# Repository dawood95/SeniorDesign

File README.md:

# SeniorDesign
Senior Design Repo

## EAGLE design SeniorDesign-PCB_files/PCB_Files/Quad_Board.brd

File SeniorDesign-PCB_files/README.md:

# Senior Design
Team 9's (Spring 2015) senior design repository.

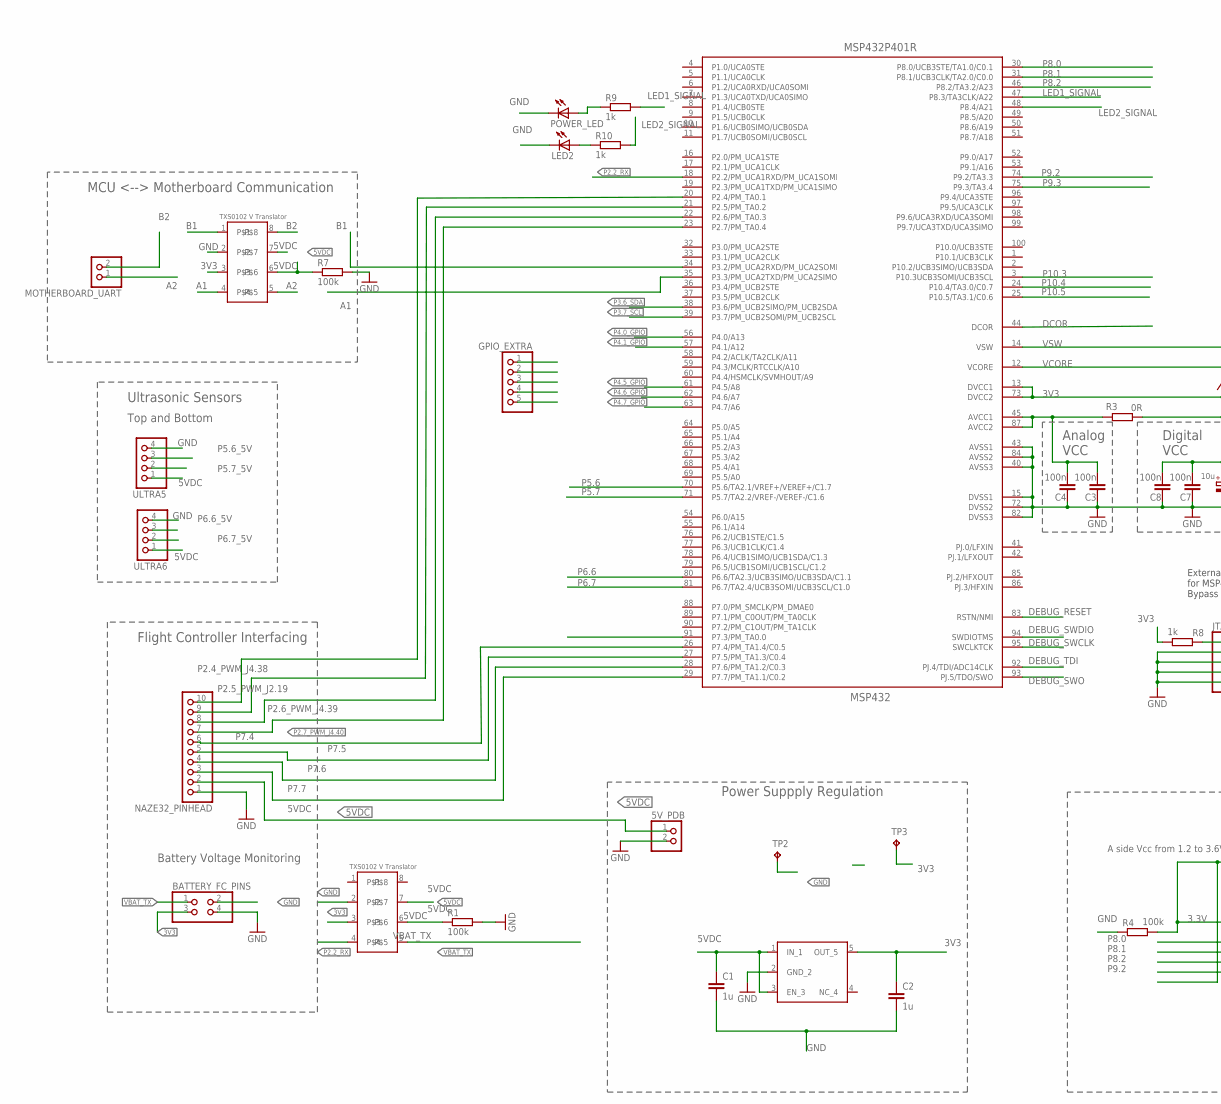
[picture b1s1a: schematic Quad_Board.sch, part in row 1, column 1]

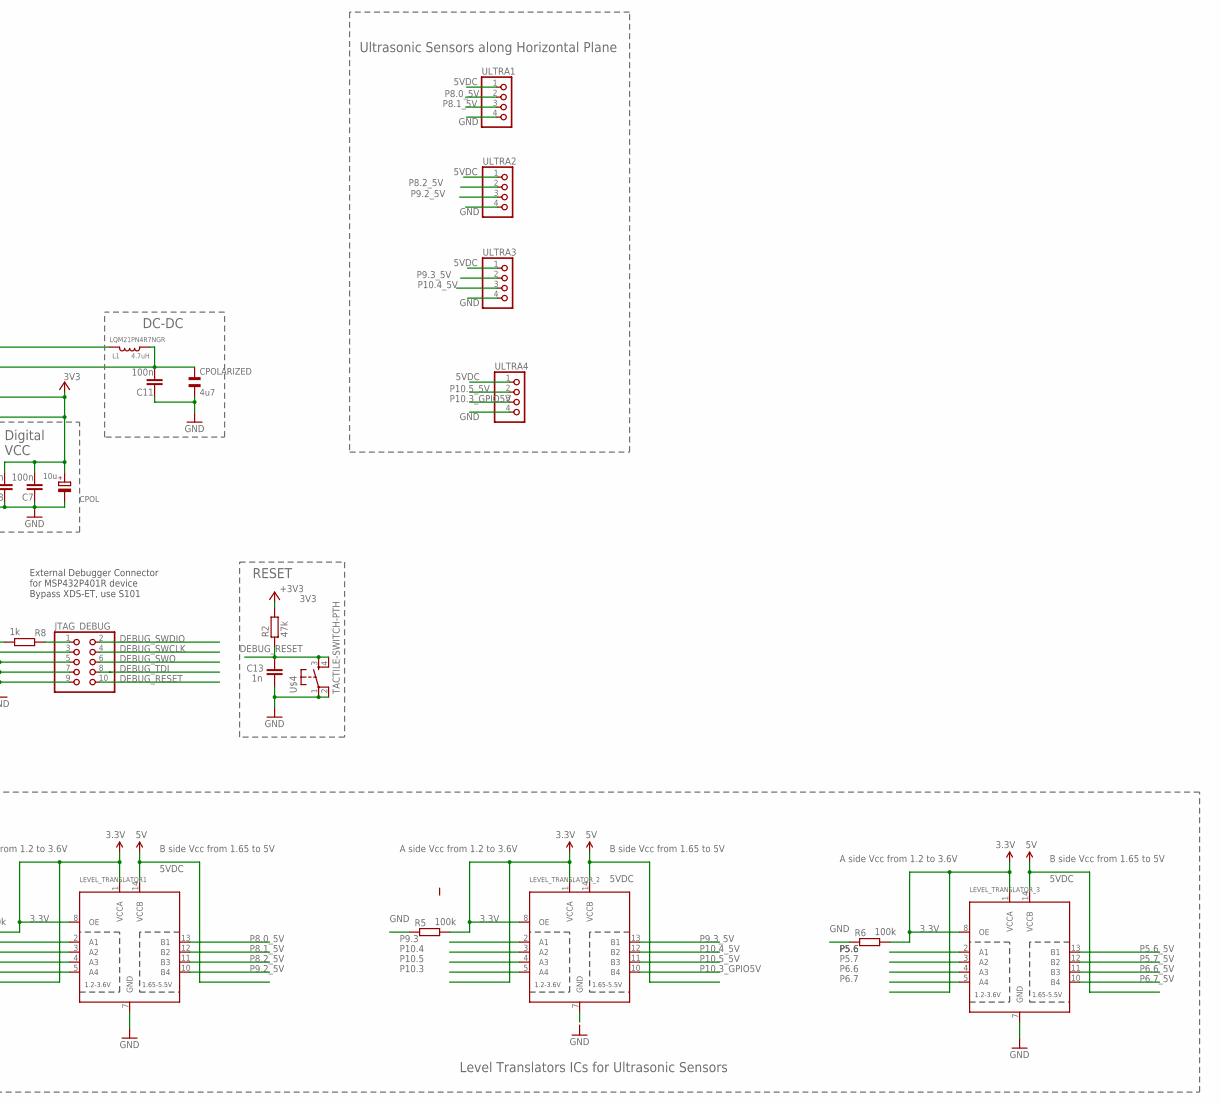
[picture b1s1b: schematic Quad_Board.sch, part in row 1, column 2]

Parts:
5V_PDB: PINHD-1X2; 1X02
BATTERY_FC_PINS: PINHD-2X2; 2X02
C1, C2: 1u; C0805
C3, C4, C7, C8, C11: 100n; C0805
C13: 1n; C0805
CPOL: 10u; A/3216-18R
CPOLARIZED: 4u7; CSMD0805
GPIO_EXTRA: PINHD-1X5; 1X05
JTAG_DEBUG: PINHD-2X5; 2X05
L1: 4.7uH; 0806
LED2: LED_E; LED_1206
LEVEL_TRANSLATOR1: TXB0104PWRSOIC14; SO14
LEVEL_TRANSLATOR_2, LEVEL_TRANSLATOR_3: TXB0104PWRSOIC14; SO14
MOTHERBOARD_UART: PINHD-1X2; 1X02
MSP432P401R: MSP432; PZ100
NAZE32_PINHEAD: PINHD-1X10; 1X10
POWER_LED: LED_E; LED_1206
R1, R4, R5, R6, R7: 100k; M1206
R2: 47k; R1206
R3: 0R; 0402
R8: 1k; R1206
R9, R10: 1k; M0805
TP2, TP3: TPB2,54; B2,54
U$1, U$3: TXS0102; DCT_R-PDSO-G8
U$2: TLV733P; SOT23-5
U$4: TACTILE-SWITCH-PTH; TAC-SWITCH-PTH
ULTRA1, ULTRA2, ULTRA3, ULTRA4, ULTRA5, ULTRA6: PINHD-1X4; 1X04

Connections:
3.3V: LEVEL_TRANSLATOR1.1 (VCCA), LEVEL_TRANSLATOR1.8 (OE), LEVEL_TRANSLATOR_2.1 (VCCA), LEVEL_TRANSLATOR_2.8 (OE), LEVEL_TRANSLATOR_3.1 (VCCA), LEVEL_TRANSLATOR_3.8 (OE), R4.2, R5.2, R6.2
3V3: BATTERY_FC_PINS.3, C2.1, C7.1, C8.1, CPOL.+, MSP432P401R.13 (DVCC1), MSP432P401R.73 (DVCC2), R2.2, R3.1, R8.1, TP3.TP, U$1.3, U$2.5 (OUT_5), U$3.3
5VDC: 5V_PDB.1, C1.1, LEVEL_TRANSLATOR1.14 (VCCB), LEVEL_TRANSLATOR_2.14 (VCCB), LEVEL_TRANSLATOR_3.14 (VCCB), NAZE32_PINHEAD.2, R1.1, R7.1, U$1.6, U$1.7, U$2.1 (IN_1), U$2.3 (EN_3), U$3.6, U$3.7, ULTRA1.1, ULTRA2.1, ULTRA3.1, ULTRA4.1, ULTRA5.1, ULTRA6.1
A1: MSP432P401R.35 (P3.3/PM_UCA2TXD/PM_UCA2SIMO), U$1.4
A2: MOTHERBOARD_UART.1, U$1.5
B1: MSP432P401R.34 (P3.2/PM_UCA2RXD/PM_UCA2SOMI), U$1.1
B2: MOTHERBOARD_UART.2, U$1.8
DCOR: MSP432P401R.44 (DCOR)
DEBUG_RESET: C13.1, JTAG_DEBUG.10, MSP432P401R.83 (RSTN/NMI), R2.1, U$4.3, U$4.4
DEBUG_SWCLK: JTAG_DEBUG.4, MSP432P401R.95 (SWCLKTCK)
DEBUG_SWDIO: JTAG_DEBUG.2, MSP432P401R.94 (SWDIOTMS)
DEBUG_SWO: JTAG_DEBUG.6, MSP432P401R.93 (PJ.5/TDO/SWO)
DEBUG_TDI: JTAG_DEBUG.8, MSP432P401R.92 (PJ.4/TDI/ADC14CLK)
GND: 5V_PDB.2, BATTERY_FC_PINS.2, BATTERY_FC_PINS.4, C1.2, C2.2, C3.2, C4.2, C7.2, C8.2, C11.2, C13.2, CPOL.-, CPOLARIZED.2, JTAG_DEBUG.3, JTAG_DEBUG.5, JTAG_DEBUG.7, JTAG_DEBUG.9, LED2.C, LEVEL_TRANSLATOR1.7 (GND), LEVEL_TRANSLATOR_2.7 (GND), LEVEL_TRANSLATOR_3.7 (GND), MSP432P401R.15 (DVSS1), MSP432P401R.40 (AVSS3), MSP432P401R.43 (AVSS1), MSP432P401R.72 (DVSS2), MSP432P401R.82 (DVSS3), MSP432P401R.84 (AVSS2), NAZE32_PINHEAD.1, POWER_LED.C, R1.2, R4.1, R5.1, R6.1, R7.2, TP2.TP, U$1.2, U$2.2 (GND_2), U$3.2, U$4.1, U$4.2, ULTRA1.4, ULTRA2.4, ULTRA3.4, ULTRA4.4, ULTRA5.4, ULTRA6.4
LED1_SIGNAL: MSP432P401R.47 (P8.3/TA3CLK/A22), R9.2
LED2_SIGNAL: MSP432P401R.48 (P8.4/A21), R10.2
unnamed: C3.1, C4.1, MSP432P401R.45 (AVCC1), MSP432P401R.87 (AVCC2), R3.2
unnamed: POWER_LED.A, R9.1
unnamed: LED2.A, R10.1
unnamed: JTAG_DEBUG.1, R8.2
P1.0/UCA0STE: MSP432P401R.4 (P1.0/UCA0STE)
P1.1/UCA0CLK: MSP432P401R.5 (P1.1/UCA0CLK)
P1.2/UCA0RXD/UCA0SOMI: MSP432P401R.6 (P1.2/UCA0RXD/UCA0SOMI)
P1.3/UCA0TXD/UCA0SIMO: MSP432P401R.7 (P1.3/UCA0TXD/UCA0SIMO)
P1.4/UCB0STE: MSP432P401R.8 (P1.4/UCB0STE)
P1.5/UCB0CLK: MSP432P401R.9 (P1.5/UCB0CLK)
P1.6/UCB0SIMO/UCB0SDA: MSP432P401R.10 (P1.6/UCB0SIMO/UCB0SDA)
P1.7/UCB0SOMI/UCB0SCL: MSP432P401R.11 (P1.7/UCB0SOMI/UCB0SCL)
P2.0/PM_UCA1STE: MSP432P401R.16 (P2.0/PM_UCA1STE)
P2.1/PM_UCA1CLK: MSP432P401R.17 (P2.1/PM_UCA1CLK)
P2.2_RX: MSP432P401R.18 (P2.2/PM_UCA1RXD/PM_UCA1SOMI), U$3.4
P2.3/PM_UCA1TXD/PM_UCA1SIMO: MSP432P401R.19 (P2.3/PM_UCA1TXD/PM_UCA1SIMO)
P2.4_PWM_J4.38: MSP432P401R.20 (P2.4/PM_TA0.1), NAZE32_PINHEAD.10
P2.5_PWM_J2.19: MSP432P401R.21 (P2.5/PM_TA0.2), NAZE32_PINHEAD.9
P2.6_PWM_J4.39: MSP432P401R.22 (P2.6/PM_TA0.3), NAZE32_PINHEAD.8
P2.7_PWM_J4.40: MSP432P401R.23 (P2.7/PM_TA0.4), NAZE32_PINHEAD.7
P3.0/PM_UCA2STE: MSP432P401R.32 (P3.0/PM_UCA2STE)
P3.1/PM_UCA2CLK: MSP432P401R.33 (P3.1/PM_UCA2CLK)
P3.4/PM_UCB2STE: MSP432P401R.36 (P3.4/PM_UCB2STE)
P3.5/PM_UCB2CLK: MSP432P401R.37 (P3.5/PM_UCB2CLK)
P3.6_SDA: MSP432P401R.38 (P3.6/PM_UCB2SIMO/PM_UCB2SDA)
P3.7_SCL: MSP432P401R.39 (P3.7/PM_UCB2SOMI/PM_UCB2SCL)
P4.0_GPIO: GPIO_EXTRA.1, MSP432P401R.56 (P4.0/A13)
P4.1_GPIO: GPIO_EXTRA.2, MSP432P401R.57 (P4.1/A12)
P4.2/ACLK/TA2CLK/A11: MSP432P401R.58 (P4.2/ACLK/TA2CLK/A11)
P4.3/MCLK/RTCCLK/A10: MSP432P401R.59 (P4.3/MCLK/RTCCLK/A10)
P4.4/HSMCLK/SVMHOUT/A9: MSP432P401R.60 (P4.4/HSMCLK/SVMHOUT/A9)
P4.5_GPIO: GPIO_EXTRA.3, MSP432P401R.61 (P4.5/A8)
P4.6_GPIO: GPIO_EXTRA.4, MSP432P401R.62 (P4.6/A7)
P4.7_GPIO: GPIO_EXTRA.5, MSP432P401R.63 (P4.7/A6)
P5.0/A5: MSP432P401R.64 (P5.0/A5)
P5.1/A4: MSP432P401R.65 (P5.1/A4)
P5.2/A3: MSP432P401R.66 (P5.2/A3)
P5.3/A2: MSP432P401R.67 (P5.3/A2)
P5.4/A1: MSP432P401R.68 (P5.4/A1)
P5.5/A0: MSP432P401R.69 (P5.5/A0)
P5.6: LEVEL_TRANSLATOR_3.2 (A1), MSP432P401R.70 (P5.6/TA2.1/VREF+/VEREF+/C1.7)
P5.6_5V: LEVEL_TRANSLATOR_3.13 (B1), ULTRA5.3
P5.7: LEVEL_TRANSLATOR_3.3 (A2), MSP432P401R.71 (P5.7/TA2.2/VREF-/VEREF-/C1.6)
P5.7_5V: LEVEL_TRANSLATOR_3.12 (B2), ULTRA5.2
P6.0/A15: MSP432P401R.54 (P6.0/A15)
P6.1/A14: MSP432P401R.55 (P6.1/A14)
P6.2/UCB1STE/C1.5: MSP432P401R.76 (P6.2/UCB1STE/C1.5)
P6.3/UCB1CLK/C1.4: MSP432P401R.77 (P6.3/UCB1CLK/C1.4)
P6.4/UCB1SIMO/UCB1SDA/C1.3: MSP432P401R.78 (P6.4/UCB1SIMO/UCB1SDA/C1.3)
P6.5/UCB1SOMI/UCB1SCL/C1.2: MSP432P401R.79 (P6.5/UCB1SOMI/UCB1SCL/C1.2)
P6.6: LEVEL_TRANSLATOR_3.4 (A3), MSP432P401R.80 (P6.6/TA2.3/UCB3SIMO/UCB3SDA/C1.1)
P6.6_5V: LEVEL_TRANSLATOR_3.11 (B3), ULTRA6.3
P6.7: LEVEL_TRANSLATOR_3.5 (A4), MSP432P401R.81 (P6.7/TA2.4/UCB3SOMI/UCB3SCL/C1.0)
P6.7_5V: LEVEL_TRANSLATOR_3.10 (B4), ULTRA6.2
P7.0/PM_SMCLK/PM_DMAE0: MSP432P401R.88 (P7.0/PM_SMCLK/PM_DMAE0)
P7.1/PM_C0OUT/PM_TA0CLK: MSP432P401R.89 (P7.1/PM_C0OUT/PM_TA0CLK)
P7.2/PM_C1OUT/PM_TA1CLK: MSP432P401R.90 (P7.2/PM_C1OUT/PM_TA1CLK)
P7.3: MSP432P401R.91 (P7.3/PM_TA0.0)
P7.4: MSP432P401R.26 (P7.4/PM_TA1.4/C0.5), NAZE32_PINHEAD.6
P7.5: MSP432P401R.27 (P7.5/PM_TA1.3/C0.4), NAZE32_PINHEAD.5
P7.6: MSP432P401R.28 (P7.6/PM_TA1.2/C0.3), NAZE32_PINHEAD.4
P7.7: MSP432P401R.29 (P7.7/PM_TA1.1/C0.2), NAZE32_PINHEAD.3
P8.0: LEVEL_TRANSLATOR1.2 (A1), MSP432P401R.30 (P8.0/UCB3STE/TA1.0/C0.1)
P8.0_5V: LEVEL_TRANSLATOR1.13 (B1), ULTRA1.2
P8.1: LEVEL_TRANSLATOR1.3 (A2), MSP432P401R.31 (P8.1/UCB3CLK/TA2.0/C0.0)
P8.1_5V: LEVEL_TRANSLATOR1.12 (B2), ULTRA1.3
P8.2: LEVEL_TRANSLATOR1.4 (A3), MSP432P401R.46 (P8.2/TA3.2/A23)
P8.2_5V: LEVEL_TRANSLATOR1.11 (B3), ULTRA2.2
P8.5/A20: MSP432P401R.49 (P8.5/A20)
P8.6/A19: MSP432P401R.50 (P8.6/A19)
P8.7/A18: MSP432P401R.51 (P8.7/A18)
P9.0/A17: MSP432P401R.52 (P9.0/A17)
P9.1/A16: MSP432P401R.53 (P9.1/A16)
P9.2: LEVEL_TRANSLATOR1.5 (A4), MSP432P401R.74 (P9.2/TA3.3)
P9.2_5V: LEVEL_TRANSLATOR1.10 (B4), ULTRA2.3
P9.3: LEVEL_TRANSLATOR_2.2 (A1), MSP432P401R.75 (P9.3/TA3.4)
P9.3_5V: LEVEL_TRANSLATOR_2.13 (B1), ULTRA3.2
P9.4/UCA3STE: MSP432P401R.96 (P9.4/UCA3STE)
P9.5/UCA3CLK: MSP432P401R.97 (P9.5/UCA3CLK)
P9.6/UCA3RXD/UCA3SOMI: MSP432P401R.98 (P9.6/UCA3RXD/UCA3SOMI)
P9.7/UCA3TXD/UCA3SIMO: MSP432P401R.99 (P9.7/UCA3TXD/UCA3SIMO)
P10.0/UCB3STE: MSP432P401R.100 (P10.0/UCB3STE)
P10.1/UCB3CLK: MSP432P401R.1 (P10.1/UCB3CLK)
P10.2/UCB3SIMO/UCB3SDA: MSP432P401R.2 (P10.2/UCB3SIMO/UCB3SDA)
P10.3: LEVEL_TRANSLATOR_2.5 (A4), MSP432P401R.3 (P10.3UCB3SOMI/UCB3SCL)
P10.3_GPIO5V: LEVEL_TRANSLATOR_2.10 (B4), ULTRA4.3
P10.4: LEVEL_TRANSLATOR_2.3 (A2), MSP432P401R.24 (P10.4/TA3.0/C0.7)
P10.4_5V: LEVEL_TRANSLATOR_2.12 (B2), ULTRA3.3
P10.5: LEVEL_TRANSLATOR_2.4 (A3), MSP432P401R.25 (P10.5/TA3.1/C0.6)
P10.5_5V: LEVEL_TRANSLATOR_2.11 (B3), ULTRA4.2
PJ.0/LFXIN: MSP432P401R.41 (PJ.0/LFXIN)
PJ.1/LFXOUT: MSP432P401R.42 (PJ.1/LFXOUT)
PJ.2/HFXOUT: MSP432P401R.85 (PJ.2/HFXOUT)
PJ.3/HFXIN: MSP432P401R.86 (PJ.3/HFXIN)
VBAT_TX: BATTERY_FC_PINS.1, U$3.5
VCORE: C11.1, CPOLARIZED.1, L1.1, MSP432P401R.12 (VCORE)
VSW: L1.2, MSP432P401R.14 (VSW)

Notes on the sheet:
LQM21PN4R7NGR
Analog
VCC
Digital
DC-DC
A side Vcc from 1.2 to 3.6V
B side Vcc from 1.65 to 5V
Level Translators ICs for Ultrasonic Sensors
Power Suppply Regulation
Ultrasonic Sensors
Ultrasonic Sensors along Horizontal Plane
Flight Controller Interfacing
MCU <--> Motherboard Communication
Battery Voltage Monitoring
Top and Bottom
External Debugger Connector for MSP432P401R device Bypass XDS-ET, use S101
RESET

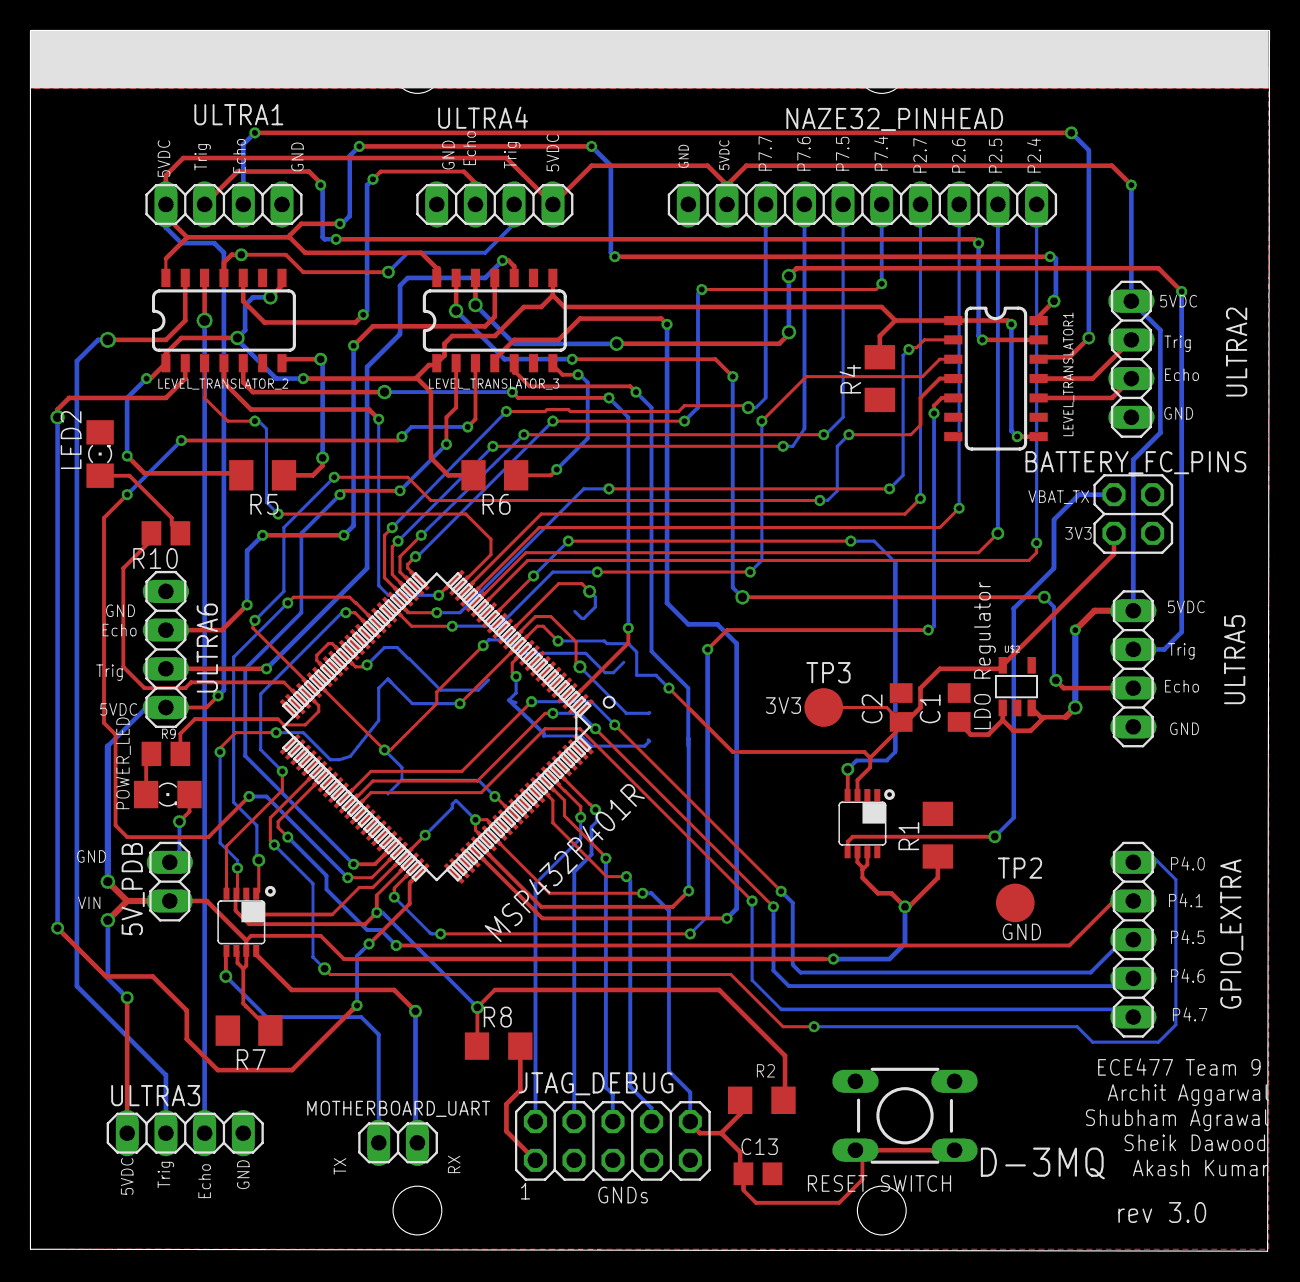
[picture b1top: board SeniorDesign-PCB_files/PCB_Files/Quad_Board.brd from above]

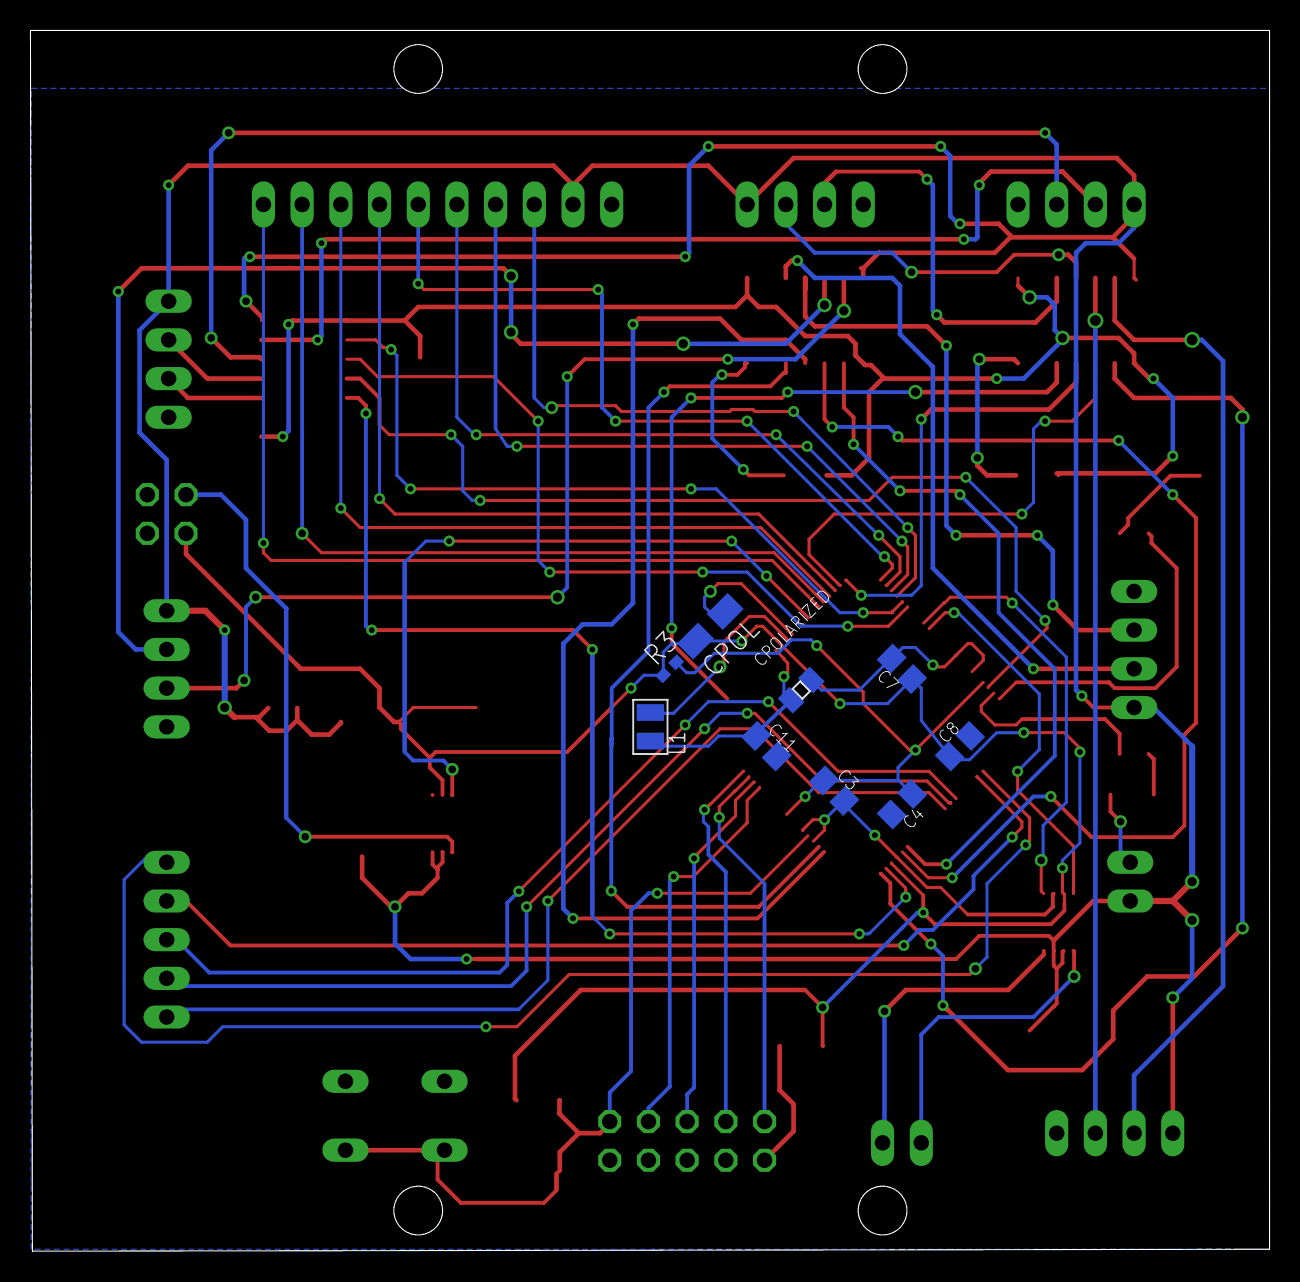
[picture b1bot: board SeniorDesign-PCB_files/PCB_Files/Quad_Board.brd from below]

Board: 2 copper layers, 81.3 x 80.1 mm, 45 parts (9 on the bottom side), 60 nets.

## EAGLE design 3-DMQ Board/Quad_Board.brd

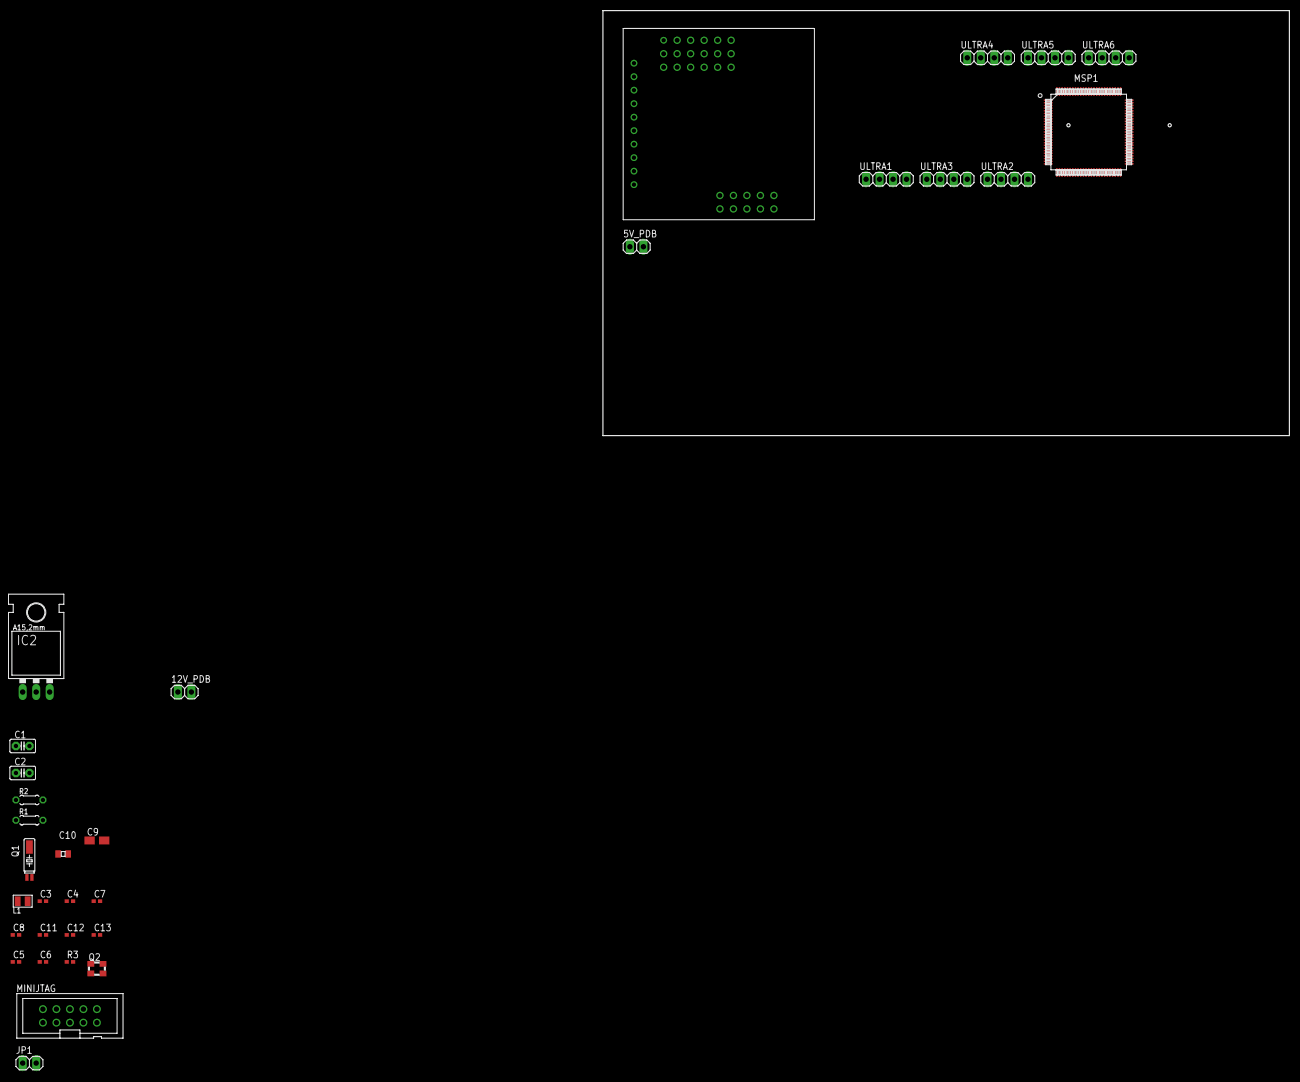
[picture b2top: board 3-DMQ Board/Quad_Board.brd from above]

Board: 2 copper layers, 129.2 x 80.0 mm, 32 parts (0 on the bottom side), 33 nets, no tracks yet.

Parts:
5V_PDB, 12V_PDB: 1X02
C1, C2: C2.5-2
C3, C4, C7, C8, C11: 100n; 0402
C5, C6: 12p; 0402
C9: 10u; A/3216-18R
C10: 4u7; CSMD0805
C12, C13: 22p; 0402
IC2: LM317MB; TO220L1
JP1: 1X02
L1: 4.7uH; 0806
MINIJTAG: PAK100/2500-10
MSP1: MSP432; PZ100
Q1: 32.768kHz; MS3V-T1R
Q2: KX-7 48MHz; KX-7
R1, R2: 0204/5
R3: 0R; 0402
U$2: NAZE32_FC; NAZE32_BOARD_FOOTPRINT
ULTRA1, ULTRA2, ULTRA3, ULTRA4, ULTRA5, ULTRA6: 1X04

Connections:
3V3: C2.1, C7.1, C8.1, C9.+, MSP1.13, MSP1.73, R1.1, R3.1
5VDC: C1.1, IC2.3, U$2.5V, ULTRA1.1, ULTRA2.1, ULTRA3.1, ULTRA4.1, ULTRA5.1, ULTRA6.1
!RST: MINIJTAG.6, MSP1.83
GND: 5V_PDB.2, C1.2, C2.2, C3.2, C4.2, C5.2, C6.2, C7.2, C8.2, C9.-, C10.2, C11.2, C12.2, C13.2, MINIJTAG.2, MSP1.15, MSP1.40, MSP1.43, MSP1.72, MSP1.82, MSP1.84, Q1.P3, R2.1, U$2.GND, ULTRA1.4, ULTRA2.4, ULTRA3.4, ULTRA4.4, ULTRA5.4, ULTRA6.4
unnamed: C3.1, C4.1, MSP1.45, MSP1.87, R3.2
unnamed: C6.1, MSP1.42, Q1.P1
unnamed: C5.1, MSP1.41, Q1.P2
unnamed: IC2.1, R2.2
unnamed: IC2.2, R1.2
P2.4_PWM_J4.38: MSP1.20, U$2.8
P2.5_PWM_J2.19: MSP1.21, U$2.7
P2.6_PWM_J4.39: MSP1.22, U$2.6
P2.7_PWM_J4.40: MSP1.23, U$2.LED/5
P5.2/XT2IN1: C13.1, MSP1.86, Q2.3
P5.3/XT2OUT1: C12.1, MSP1.85, Q2.1
P5.4_IO_J3.29: MSP1.68, ULTRA5.2
P5.5_IO_J3.30: MSP1.69, ULTRA6.2
P5.6_PWM_J4.37: MSP1.70, ULTRA5.3
P5.7_IO_J2.17: MSP1.71, ULTRA6.3
P7.4: MSP1.26, U$2.U2RX/4
P7.5: MSP1.27, U$2.U2TX/3
P7.6: MSP1.28, U$2.2
P7.7: MSP1.29, U$2.PPM
P8.2: MSP1.46, ULTRA1.3
P9.1: MSP1.53, ULTRA2.2
P9.2: MSP1.74, ULTRA2.3
P10.5: MSP1.25, ULTRA4.3
TCK_SWCLK: MINIJTAG.1, MSP1.95
TDI: MINIJTAG.9, MSP1.92
TDO_SWO: MINIJTAG.3, MSP1.93
TMS_SWDIO: MINIJTAG.5, MSP1.94
VCORE: C10.1, C11.1, L1.1, MSP1.12
VSW: L1.2, MSP1.14

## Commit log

2016-02-24 Old PCB schematic
2016-02-24 Board Layout Under Progress
2016-02-27 Board Layout in Routing Stage
2016-02-28 PCB Layout Rev1 90% done
2016-02-28 MCU Icaps routing remaining
2016-02-29 PCB Updates
2016-02-29 Added Battery Monitroing Circuit
2016-03-01 Design Review PCB
2016-03-01 Design Review PCB Update
2016-03-08 Updates in layout
2016-03-09 started working on code for mapping
2016-03-09 made basic server
2016-03-09 basic client
2016-03-09 basic client modified
2016-03-09 working on map code
2016-03-10 Completed Schematic for PCB submission
2016-03-11 Updates in PCB Schematic and Layout
2016-03-12 working on 3d mapping
2016-03-12 Routing almost finalized
2016-03-12 preliminary silk screen added
2016-03-12 Adding more silscreen info
2016-03-12 P+Completed PCB barring reference IC ppoints
2016-03-12 Pre Submission PCB
2016-03-19 added ignore file
2016-04-07 UART, PWM and Input Capture test code
2016-04-08 Updates in FC PWM
2016-04-10 New PCB design
2016-04-10 Re-designed layout
2016-04-13 Byte encoded vbat to Motherboard
2016-04-15 Ping))) Ultra Sensor && HCSR04
2016-04-15 Bugs in integrated code w/ Ultra sensors

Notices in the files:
parts and their libraries:
SparkFun-DigitalIC: Licensing: CC v3.0 Share-Alike You are welcome to use this library for commercial purposes.
GeekAmmo: Licensing:Creative Commons ShareAlike 4.0 International - https://creativecommons.org/licenses/by-sa/4.0
